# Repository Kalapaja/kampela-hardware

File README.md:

# Kampela

## Reasonably secure hardware signer for the [Polkadot](https://polkadot.network) ecosystem

### Hardware design schematics and supplementary files

##### Note on repo history

This repo has been extracted from https://github.com/Alzymologist/kampela in September 2023 as a part of the repo modularization effort.

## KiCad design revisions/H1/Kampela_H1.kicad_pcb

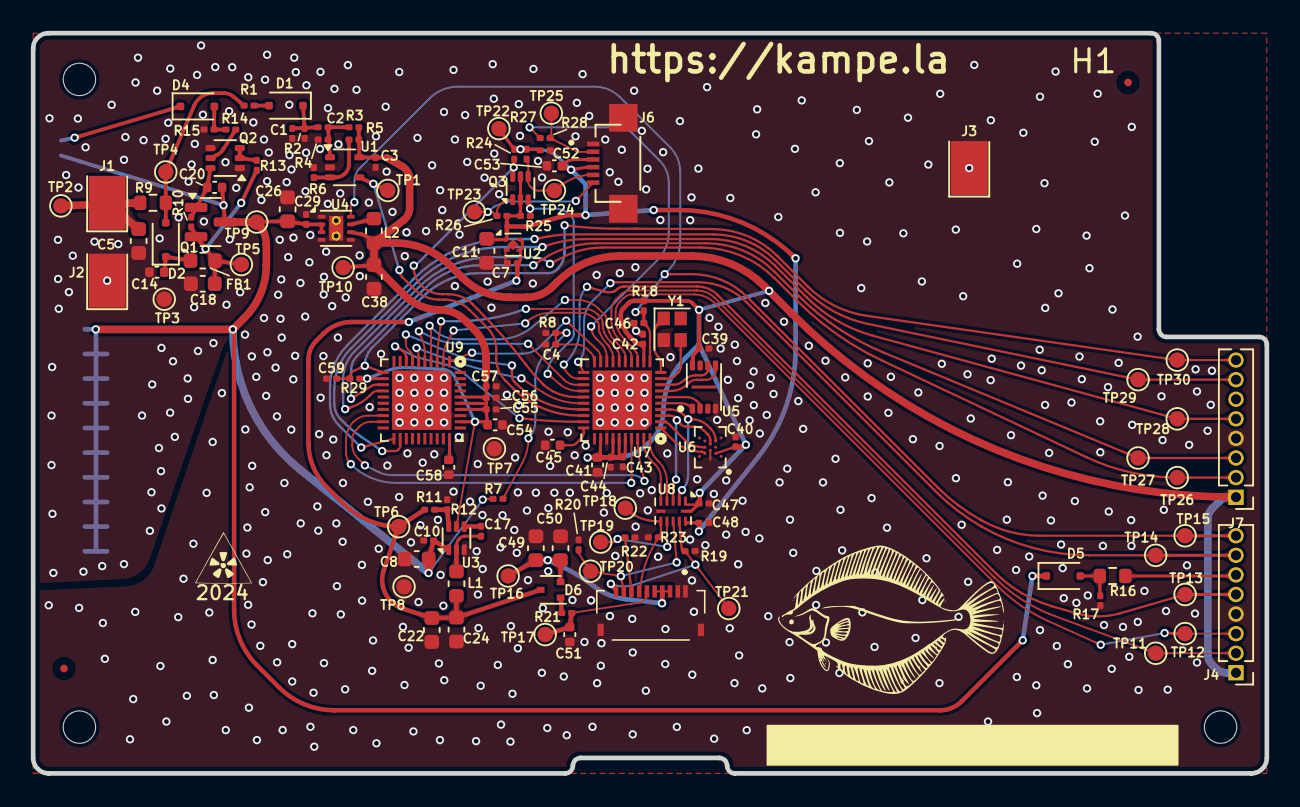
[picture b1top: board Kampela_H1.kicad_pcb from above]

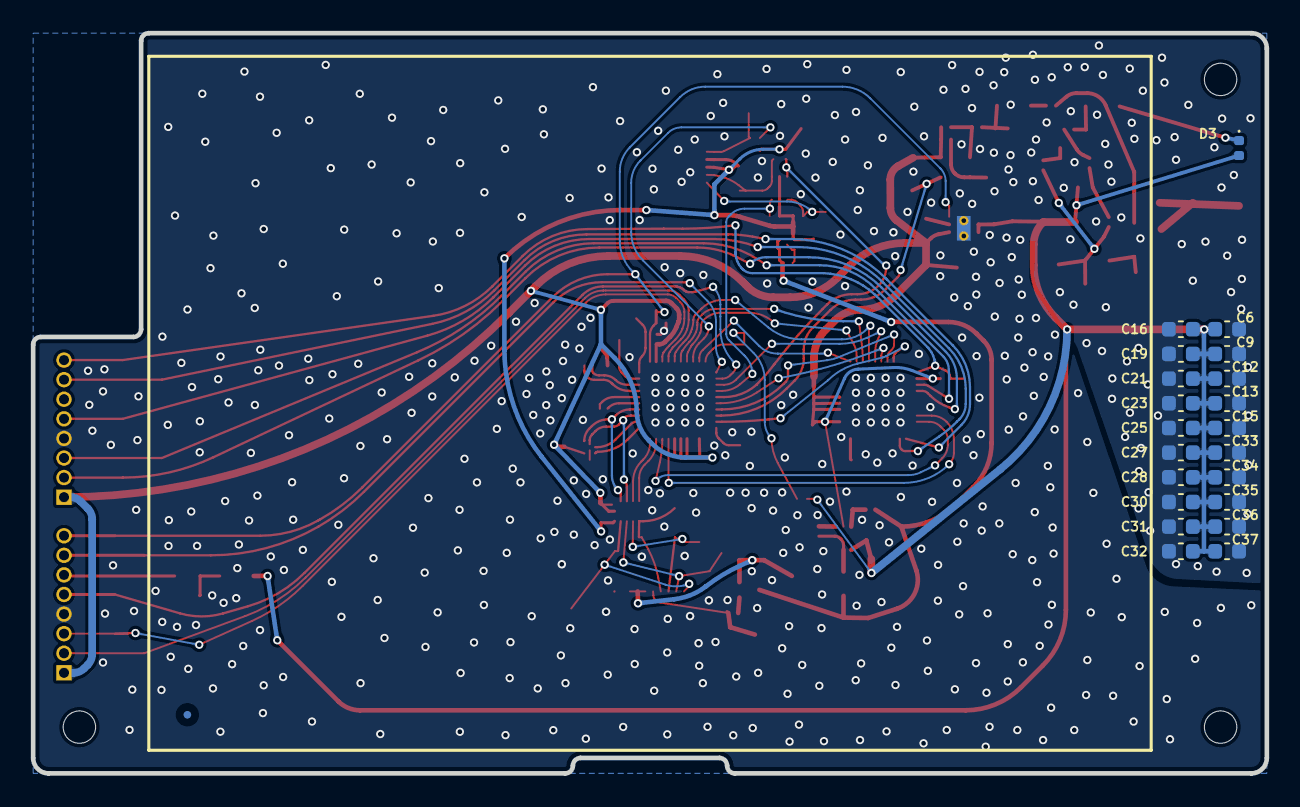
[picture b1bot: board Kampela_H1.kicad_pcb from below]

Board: 2 copper layers, 80.0 x 48.0 mm, 153 parts (22 on the bottom side), 73 nets.

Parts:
C1, C2: 100p; C_0201_0603Metric
C3, C4, C7, C10, C17, C29, C39, C40, C42, C43, C44, C46, C47, C48, C52, C55, C56, C57, C59: 0.1; C_0201_0603Metric
C5: 15p; C_0603_1608Metric
C6, C9, C12, C13, C15, C16, C19, C21, C23, C25, C27, C28, C30, C31, C32, C33, C34, C35, C36, C37: 22x16; C_0603_1608Metric
C8, C18, C26: 10x25; C_0603_1608Metric
C11, C22, C24, C38, C49, C50: 22x6.3; C_0603_1608Metric
C14, C20: 1x50; C_0402_1005Metric
C41, C45, C51, C53, C54, C58: 1x6.3; C_0402_1005Metric
D1, D5: BAT54WS; D_SOD-323F
D2: BAS70WS; D_SOD-323F
D3: RED; LED_0402_1005Metric
D4: D3Z13BF-7; D_SOD-323F
D6: BAT54AW; SOT-523
FB1: BLM18KG102SN1D; L_0603_1608Metric
FID1, FID2, FID4: Fiducial; Fiducial_0.5mm_Mask1.5mm
H1, H2, H3: MountingHole; MountingHole_2.1mm
J1, J2, J3: E_ANT; TestPoint_Pad_2.4x3.5mm
J4, J7: Conn_01x08; PinHeader_1x08_P1.27mm_Vertical
J5: FPC 10 TE1-2328702-0; TE_123287020
J6: TOUCH; HRS_FH34SRJ-6S-0.5SH(50)
L1, L2: 4.7uH; L_0603_1608Metric
Q1: NTR5105PT1G; SOT-23
Q2: BC846BS; SOT-363_SC-70-6
Q3: SSM6N35AFE; SOT-563
R1, R12, R15, R17, R18, R24, R25, R26, R27, R28, R29: 10K; R_0201_0603Metric
R2, R5, R11: 52.3K; R_0201_0603Metric
R3, R4, R10, R13, R19, R20, R22, R23: 100K; R_0201_0603Metric
R6, R14: 46.4K; R_0201_0603Metric
R7, R21: 1M; R_0201_0603Metric
R8: 150K; R_0201_0603Metric
R9, R16: 2.2; R_0603_1608Metric
TP1, TP2, TP3, TP4, TP5, TP6, TP7, TP8, TP9, TP10, TP11, TP12, TP13, TP14, TP15, TP16, TP17, TP18, TP19, TP20, TP21, TP22, TP23, TP24, TP25, TP26, TP27, TP28, TP29, TP30: TestPoint; TestPoint_Pad_D1.0mm
U1: LMV7271; SOT-353_SC-70-5
U2: NCP170AMX180TBG; OnSemi_XDFN4-1EP_1.0x1.0mm_EP0.52x0.52mm
U3: AP62250Z6; SOT-563
U4: TPS62171DSG; WSON-8-1EP_2x2mm_P0.5mm_EP0.9x1.6mm_ThermalVias
U5: APS6404L-SQN; SON-8-1EP_3x2mm_P0.5mm_EP1.4x1.6mm
U6: AT25XE321D-UUN-T; WLCSP 12-ball 3 x 2 x 3 Array
U7, U9: EFM32PG23B200F512IM40; QFN-40_EP_5x5_Pitch0.4mm
U8: TXU0104PW; Texas_R-PUQFN-N12
Y1: 39MHz; Crystal_SMD_2016-4Pin_2.0x1.6mm

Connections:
+1V8: C3.1, C38.1, C39.2, C40.2, C41.1, C42.2, C43.2, C44.2, C47.1, C54.1, C55.2, C56.2, C57.2, J4.1, J7.1, L2.2, R3.2, R5.2, R18.2, R29.2, TP10.1, U1.5 (V+), U3.5 (EN), U4.6 (VOS), U5.8 (VCC), U6.B2 (VCC), U7.12 (DVDD), U7.32 (VREGVDD), U7.34 (DVDD), U7.35 (AVDD), U7.36 (IOVDD), U8.1 (VCCA), U8.12 (OE), U9.12 (DVDD), U9.32 (VREGVDD), U9.34 (DVDD), U9.35 (AVDD), U9.36 (IOVDD)
+3V0: C11.2, C48.1, C52.2, C53.1, J6.3, J6.4, Q3.2 (G), Q3.5 (G), R24.2, R25.2, R26.2, R27.2, TP22.1, U2.1 (OUT), U8.11 (VCCB)
+5V: C7.2, C22.1, C24.2, D6.3, L1.2, R11.2, TP6.1, U2.3 (EN), U2.4 (IN)
/Display/CS: U7.40 (PD00), U8.4 (A3)
/Display/EXTIN: U7.39 (PD01), U8.5 (A4)
/Display/H_CS: J5.8, R22.2, TP19.1, U8.8 (B3)
/Display/H_EXTIN: J5.7, R23.2, TP18.1, U8.7 (B4)
/Display/H_SCK: J5.10, R19.2, TP21.1, U8.10 (B1)
/Display/H_SDI: J5.9, R20.2, TP20.1, U8.9 (B2)
/Display/INT: R28.1, U7.18 (PB01)
/Display/SCL: Q3.3 (D), R25.1, U7.24 (PA04)
/Display/SDA: Q3.6 (D), R24.1, U7.25 (PA05)
/Display/T_INT: J6.2, R28.2, TP25.1
/Display/T_SCL: J6.5, Q3.4 (S), R27.1, TP24.1
/Display/T_SDA: J6.6, Q3.1 (S), R26.1, TP23.1
/MCU SEC/ALEPH: U7.19 (PB00), U9.1 (PC00)
/MCU SEC/BET: U7.17 (PB02), U9.2 (PC01)
/MCU SEC/DALET: U7.15 (PB04), U9.4 (PC03)
/MCU SEC/DATA: TP1.1, U1.4, U7.28 (PA08)
/MCU SEC/E_MISO: U6.D4 (IO1/SO), U7.2 (PC01)
/MCU SEC/E_MOSI: U6.E3 (SI/IO0), U7.3 (PC02), U8.3 (A2)
/MCU SEC/E_SCK: U6.F2 (SCK), U7.4 (PC03), U8.2 (A1)
/MCU SEC/FLASH_CS: U6.B4 (~CS), U7.1 (PC00)
/MCU SEC/GIMEL: U7.16 (PB03), U9.3 (PC02)
/MCU SEC/HE: U7.23 (PA03), U9.5 (PC04)
/MCU SEC/HET: U7.29 (PA09), U9.8 (PC07)
/MCU SEC/P_GOOD: C46.2, J4.8, R18.1, TP15.1, U4.8 (PG), U7.11 (~RESET)
/MCU SEC/P_IN: J4.6, R16.1
/MCU SEC/RAM_CS: U5.1 (~CE), U7.5 (PC04)
/MCU SEC/RX: J4.2, TP11.1, U7.14 (PB05)
/MCU SEC/R_MISO: U5.2 (SO/SIO), U7.6 (PC05)
/MCU SEC/R_MOSI: U5.5 (SI/SIO), U7.7 (PC06)
/MCU SEC/R_SCK: U5.6 (SCLK), U7.8 (PC07)
/MCU SEC/SWDCK: J4.7, TP14.1, U7.21 (PA01)
/MCU SEC/SWDIO: J4.5, TP13.1, U7.22 (PA02)
/MCU SEC/TET: U7.38 (PD02), U9.19 (PB00)
/MCU SEC/TX: J4.3, TP12.1, U7.13 (PB06)
/MCU SEC/VAV: U7.26 (PA06), U9.6 (PC05)
/MCU SEC/V_CHK: C4.2, R7.1, R8.2, U7.20 (PA00)
/MCU SEC/YOD: U7.37 (PD03), U9.18 (PB01)
/MCU SEC/ZAYIN: U7.27 (PA07), U9.7 (PC06)
/MCU UI/P_GOOD: C59.2, J7.8, R29.1, TP30.1, U9.11 (~RESET)
/MCU UI/RX: J7.2, TP26.1, U9.14 (PB05)
/MCU UI/SWDCK: J7.7, TP29.1, U9.21 (PA01)
/MCU UI/SWDIO: J7.5, TP28.1, U9.22 (PA02)
/MCU UI/TX: J7.3, TP27.1, U9.13 (PB06)
/Power/OUT_DT: D2.2 (A), R1.1, R9.2, TP4.1
GND: C1.1, C3.2, C4.1, C5.2, C6.2, C7.1, C8.2, C9.2, C10.1, C11.1, C12.2, C13.2, C14.2, C15.2, C16.2, C18.2, C19.2, C21.2, C22.2, C23.2, C24.1, C25.2, C26.2, C27.2, C28.2, C29.1, C30.2, C31.2, C32.2, C33.2, C34.2, C35.2, C36.2, C37.2, C38.2, C39.1, C40.1, C41.2, C42.1, C43.1, C44.1, C45.2, C46.1, C47.2, C48.2, C49.1, C50.1, C51.2, C52.1, C53.2, C54.2, C55.1, C56.1, C57.1, C58.2, C59.1, J2.1, J3.1, J4.4, J5.1, J5.2, J5.MP1, J5.MP2, J6.1, J6.S2 (S), J7.4, Q2.1 (E1), Q2.4 (E2), R2.1, R4.1, R6.1, R8.1, R12.1, R15.1, R17.1, R19.1, R20.1, R22.1, R23.1, TP3.1, TP7.1, TP8.1, U1.2 (V-), U2.2 (GND), U2.5 (GND), U3.3 (GND), U4.1 (PGND), U4.4 (AGND), U4.5 (FB), U4.9 (PAD), U5.4 (VSS), U6.C3 (GND), U7.33 (VREGVSS), U7.41 (VSS), U8.6 (GND), U9.33 (VREGVSS), U9.41 (VSS), Y1.2
HV: C6.1, C8.1, C9.1, C10.2, C12.1, C13.1, C15.1, C16.1, C19.1, C20.2, C21.1, C23.1, C25.1, C26.1, C27.1, C28.1, C29.2, C30.1, C31.1, C32.1, C33.1, C34.1, C35.1, C36.1, C37.1, D3.2 (A), D5.1 (K), Q1.3 (D), R7.2, TP9.1, U3.1 (VIN), U4.2 (VIN), U4.3 (EN)
unnamed: C49.2, C50.2, D6.2, J5.3, J5.4, J5.5, TP16.1
unnamed: C51.1, J5.6, R21.1, TP17.1
unnamed: D1.2 (A), R1.2
unnamed: C1.2, C2.2, D1.1 (K), R2.2
unnamed: C14.1, D2.1 (K), FB1.2
unnamed: D3.1 (K), D4.1 (K)
unnamed: D4.2 (A), R14.1, R15.2
unnamed: D5.2 (A), R16.2, R17.2
unnamed: D6.1, R21.2
unnamed: C5.1, J1.1, R9.1, TP2.1
unnamed: C20.1, Q1.1 (G), Q2.6 (C1), R10.2
unnamed: C18.1, FB1.1, Q1.2 (S), R10.1, R13.2, TP5.1
unnamed: Q2.2 (B1), Q2.3 (C2), R13.1
unnamed: Q2.5 (B2), R14.2
unnamed: C2.1, R3.1, R4.2, U1.1 (+)
unnamed: R5.1, R6.2, U1.3 (-)
unnamed: C17.1, U3.4 (BST)
unnamed: R11.1, R12.2, U3.6 (FB)
unnamed: C17.2, L1.1, U3.2 (SW)
unnamed: L2.1, U4.7 (SW)
unnamed: C45.1, U7.30 (CAP)
unnamed: U7.9 (HFXTAL_I), Y1.3
unnamed: U7.10 (HFXTAL_O), Y1.1
unnamed: C58.1, U9.30 (CAP)

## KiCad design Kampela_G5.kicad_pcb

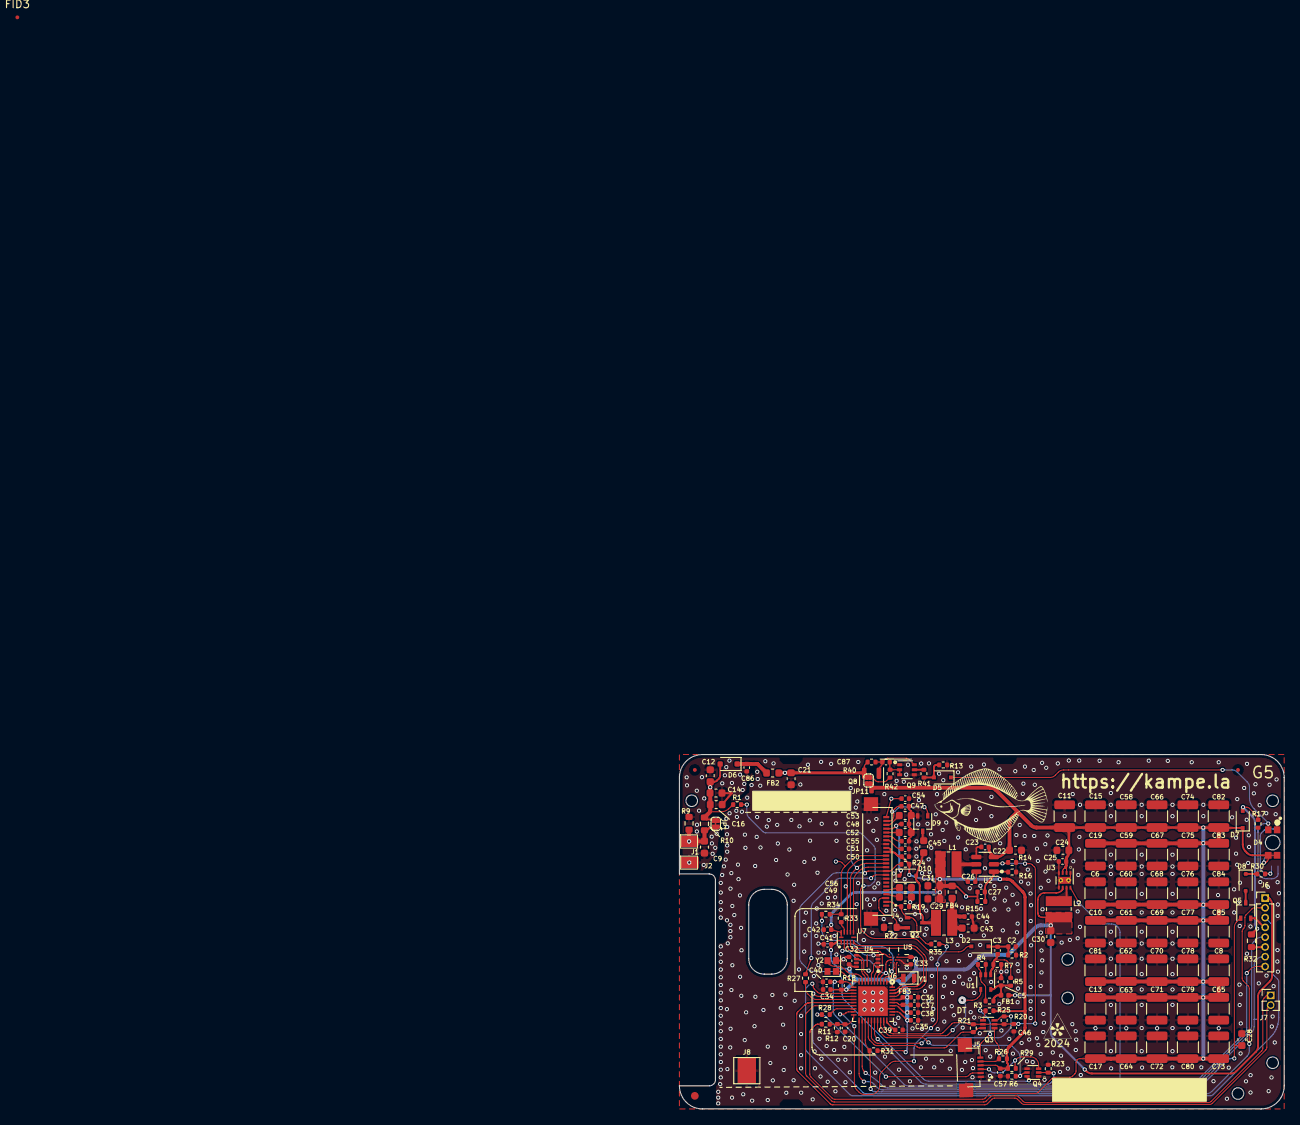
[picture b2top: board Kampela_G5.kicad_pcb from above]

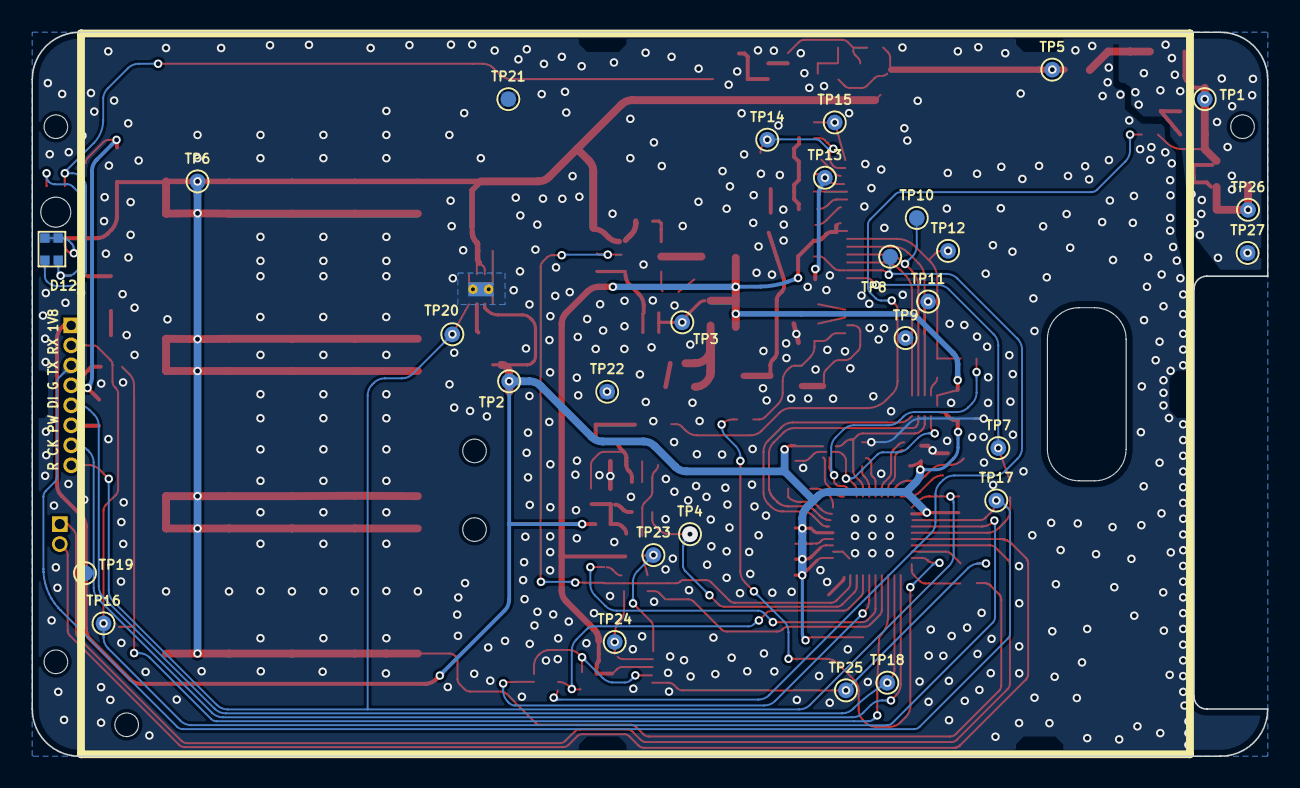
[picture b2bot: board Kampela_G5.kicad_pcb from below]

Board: 2 copper layers, 78.5 x 46.0 mm, 194 parts (28 on the bottom side), 86 nets.

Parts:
C2, C3, C27: 100p; C_0402_1005Metric
C5, C20, C23, C25, C26, C32, C33, C35, C36, C37, C38, C40, C41, C42, C46: 0.1u; C_0402_1005Metric
C6, C8, C10, C11, C13, C15, C17, C19, C58, C59, C60, C61, C62, C63, C64, C65, C66, C67, C68, C69, C70, C71, C72, C73, C74, C75, C76, C77, C78, C79, C80, C81, C82, C83, C84, C85: 47x16; C_1210_3225Metric
C9: 15p; C_0603_1608Metric
C12, C14: 47; C_0603_1608Metric
C16: 100; C_0603_1608Metric
C21: 10x25; C_0603_1608Metric
C22, C24: 10x16; C_0603_1608Metric
C28, C43, C45, C49, C52, C53, C56: 4.7x25; C_0603_1608Metric
C29, C30, C31: 22x6.3; C_0603_1608Metric
C34, C39, C50, C51, C55, C57: 1x6.3; C_0402_1005Metric
C44: 0.1; C_0402_1005Metric
C47, C48, C54, C86, C87: 1x50; C_0402_1005Metric
D2, D7, D10: BAT54WS; D_SOD-323F
D4: 156125RG73000; SMD4_WL-SBRW-1205_REV-MOUNT_WRE
D5: D3Z13BF-7; D_SOD-323F
D6: BAS70WS; D_SOD-323F
D8: D3Z5V1BF-7; D_SOD-323F
D9: BAS70-04W; SOT-323_SC-70
D12: SB0603WC01-RG; LED_DUAL_0603
FB1, FB3: BLM15AG102SZ1D; L_0402_1005Metric
FB2, FB4: BLM18KG102SN1D; L_0603_1608Metric
FID1, FID2, FID3, FID4: Fiducial; Fiducial_0.5mm_Mask1.5mm
H1, H2, H3: MountingHole; MountingHole_2.1mm
J1, J2, J8: E_ANT; TestPoint_Pad_2.4x3.5mm
J4: E2154CS0C1; GDEY027T91-T01_bended
J5: TOUCH; HRS_FH34SRJ-6S-0.5SH(50)
J6: Conn_01x08; PinHeader_1x08_P1.27mm_Vertical
J7: Conn_01x02; PinHeader_1x02_P1.27mm_Vertical
JP1, JP11: SolderJumper_2_Open; SolderJumper_0.8.x1mm
L1: 3.3uH; L_Wuerth_MAPI-3015
L2: 2.2uH; L_Wuerth_MAPI-3015
L3: NR3015T100M; L_Wuerth_MAPI-3015
Q2: PMF250XNEX; SOT-323_SC-70
Q3, Q4: SSM6N35AFE; SOT-563
Q5: NX138BKWX; SOT-323_SC-70
Q8: NTR5105PT1G; SOT-23
Q9: BC846BS; SOT-363_SC-70-6
R1, R6, R17, R18, R23, R24, R25, R26, R27, R28, R29: 10K; R_0402_1005Metric
R2, R3, R16: 52.3K; R_0402_1005Metric
R4, R41: 47K; R_0402_1005Metric
R5, R7, R40, R42: 100K; R_0402_1005Metric
R9: 1K; R_0603_1608Metric
R10, R32: 2.2; R_0603_1608Metric
R11: 976K; R_0402_1005Metric
R12, R14: 150K; R_0402_1005Metric
R13, R20, R21, R34, R35: 1K; R_0402_1005Metric
R15: 130K; R_0402_1005Metric
R19, R31: 470K; R_0402_1005Metric
R22: 0.47R; R_0603_1608Metric
R30, R33: 100; R_0402_1005Metric
TP1, TP2, TP3, TP4, TP5, TP6, TP7, TP8, TP9, TP10, TP11, TP12, TP13, TP14, TP15, TP16, TP17, TP18, TP19, TP20, TP21, TP22, TP23, TP24, TP25, TP26, TP27: TestPoint; TestPoint_Pad_D1.0mm
U1: LMV7271; SOT-353_SC-70-5
U2: AP63200WU; TSOT-23-6
U3: TPS62171DSG; WSON-8-1EP_2x2mm_P0.5mm_EP0.9x1.6mm_ThermalVias
U4: APS6404L-SQN; SON-8-1EP_3x2mm_P0.5mm_EP1.4x1.6mm
U5: AT25XE321D-UUN-T; WLCSP 12-ball 3 x 2 x 3 Array
U6: EFM32PG23B200F512IM40; QFN-40_EP_5x5_Pitch0.4mm
U7: TXU0104PW; Texas_R-PUQFN-N12
Y1: FC2012AN; Crystal_SMD_2012-2Pin_2.0x1.2mm
Y2: 39MHz; Crystal_SMD_2016-4Pin_2.0x1.6mm

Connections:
+1V8: C30.2, C32.1, C33.1, C34.2, C35.1, C36.1, C38.1, C41.2, FB1.1, FB3.2, J6.1, L2.2, R18.2, R31.1, TP2.1, U3.6 (VOS), U4.8 (VCC), U5.B2 (VCC), U6.12 (DVDD), U6.32 (VREGVDD), U6.34 (DVDD), U6.36 (IOVDD), U7.1 (VCCA)
+2V8: C27.1, C29.2, C31.2, C42.1, C50.2, C57.1, FB4.2, J4.15, J4.16, J5.4, L1.2, R15.1, R24.2, R25.1, R26.1, R29.2, TP3.1, U7.11 (VCCB), U7.12 (OE)
/Cap Block/HV: C6.2, C8.2, C10.2, C11.2, C13.2, C15.2, C17.2, C19.2, C22.2, C23.1, C24.2, C25.1, C58.2, C59.2, C60.2, C61.2, C62.2, C63.2, C64.2, C65.2, C66.2, C67.2, C68.2, C69.2, C70.2, C71.2, C72.2, C73.2, C74.2, C75.2, C76.2, C77.2, C78.2, C79.2, C80.2, C81.2, C82.2, C83.2, C84.2, C85.2, D4.3 (A2), D4.4 (A1), D7.1 (K), D12.2 (K1), D12.4 (K2), JP11.1 (A), Q8.3 (D), R11.1, TP6.1, U2.3 (IN), U3.2 (VIN), U3.3 (EN)
/Display/2V8_EN: C46.1, Q3.2 (G), Q3.5 (G), R14.2, R20.2, R21.2, U2.2 (EN), U6.29 (PA09)
/Display/BUSY: R27.2, U6.15 (PB04)
/Display/E_BUSY: J4.9, R27.1, TP7.1
/Display/E_CS: U6.38 (PD02), U7.4 (A3)
/Display/E_D/C: U6.37 (PD03), U7.5 (A4)
/Display/E_MISO: R34.1, U5.D4 (IO1/SO), U6.2 (PC01)
/Display/E_RES: J4.10, Q4.6 (D), R24.1, TP8.1
/Display/E_SCK: U5.F2 (SCK), U6.4 (PC03), U7.3 (A2)
/Display/E_SDI: U5.E3 (SI/IO0), U6.3 (PC02), U7.2 (A1)
/Display/GDR: J4.2, Q2.1 (G), R19.1, R35.1
/Display/H_CS: J4.12, TP10.1, U7.8 (B3)
/Display/H_D/C: J4.11, TP9.1, U7.7 (B4)
/Display/H_SCK: J4.13, TP11.1, U7.9 (B2)
/Display/H_SDI: J4.14, R33.1, R34.2, TP12.1
/Display/INT: R28.2, U6.18 (PB01)
/Display/POW: C43.2, C44.1, FB4.1, L3.1
/Display/PREVGH: C48.1, D10.1 (K), J4.21, TP13.1
/Display/PREVGL: C47.1, D9.1, J4.23, TP14.1
/Display/RES: Q4.2 (G), R23.2, U6.26 (PA06)
/Display/RESE: J4.3, Q2.2 (S), R22.1
/Display/RES_TC: Q4.5 (G), R6.2, U6.27 (PA07)
/Display/SCL: Q3.3 (D), R21.1, U6.24 (PA04)
/Display/SDA: Q3.6 (D), R20.1, U6.25 (PA05)
/Display/T_INT: J5.2, R28.1, TP25.1
/Display/T_RES: J5.3, Q4.3 (D), R29.1
/Display/T_SCL: J5.5, Q3.4 (S), R26.2, TP24.1
/Display/T_SDA: J5.6, Q3.1 (S), R25.2, TP23.1
/Display/VCOM: C54.2, J4.24, TP15.1
/MCU/DATA: TP4.1, U1.4, U6.28 (PA08)
/MCU/FLASH_CS: U5.B4 (~CS), U6.1 (PC00)
/MCU/P_GOOD: C40.1, J6.8, R18.1, TP20.1, U3.8 (PG), U6.11 (~RESET)
/MCU/P_IN: J6.6, R32.1
/MCU/RAM_CS: U4.1 (~CE), U6.5 (PC04)
/MCU/RX: J6.2, TP16.1, U6.14 (PB05)
/MCU/R_MISO: U4.2 (SO/SIO), U6.6 (PC05)
/MCU/R_MOSI: U4.5 (SI/SIO), U6.7 (PC06)
/MCU/R_SCK: U4.6 (SCLK), U6.8 (PC07)
/MCU/SWDCK: J6.7, TP19.1, U6.21 (PA01)
/MCU/SWDIO: J6.5, TP18.1, U6.22 (PA02)
/MCU/TX: J6.3, TP17.1, U6.13 (PB06)
/MCU/V_CHK: C20.1, R11.2, R12.1, U6.20 (PA00)
/MCU/~MCU_OK: C28.2, Q5.1 (G), R31.2, U6.23 (PA03)
/Power/IN_DT: C12.1, C14.1, C16.1, D6.2 (A), JP1.1 (A), R1.1, R10.2, TP1.1
GND: C2.2, C5.1, C6.1, C8.1, C9.2, C10.1, C11.1, C12.2, C13.1, C14.2, C15.1, C16.2, C17.1, C19.1, C20.2, C21.1, C22.1, C23.2, C24.1, C25.2, C28.1, C29.1, C30.1, C31.1, C32.2, C33.2, C34.1, C35.2, C36.2, C37.2, C38.2, C39.1, C40.2, C41.1, C42.2, C43.1, C44.2, C46.2, C47.2, C48.2, C49.1, C50.1, C51.1, C52.1, C53.1, C54.1, C55.1, C56.1, C57.2, C58.1, C59.1, C60.1, C61.1, C62.1, C63.1, C64.1, C65.1, C66.1, C67.1, C68.1, C69.1, C70.1, C71.1, C72.1, C73.1, C74.1, C75.1, C76.1, C77.1, C78.1, C79.1, C80.1, C81.1, C82.1, C83.1, C84.1, C85.1, C86.2, D9.2, J2.1, J4.8, J4.17, J4.S2 (S), J5.1, J5.S2 (S), J6.4, J8.1, Q4.1 (S), Q4.4 (S), Q5.2 (S), Q9.1 (E1), Q9.4 (E2), R2.2, R4.2, R6.1, R7.2, R9.1, R12.2, R13.2, R14.1, R16.2, R17.2, R19.2, R22.2, R23.1, TP21.1, TP22.1, TP27.1, U1.2 (V-), U2.4 (GND), U3.1 (PGND), U3.4 (AGND), U3.5 (FB), U3.9 (PAD), U4.4 (VSS), U5.C3 (GND), U6.33 (VREGVSS), U6.41 (VSS), U7.6 (GND), Y2.2
unnamed: C45.1, D9.3
unnamed: D2.2 (A), R1.2
unnamed: C2.1, C3.2, D2.1 (K), R2.1
unnamed: D5.2 (A), R13.1, R41.2
unnamed: C86.1, D6.1 (K), FB2.2
unnamed: D7.2 (A), R17.1, R32.2
unnamed: D8.2 (A), Q5.3 (D)
unnamed: D8.1 (K), R30.2
unnamed: C45.2, D10.2 (A), L3.2, Q2.3 (D)
unnamed: D4.2 (K2), D5.1 (K), D12.1 (A1)
unnamed: D4.1 (K1), D12.3 (A2), R30.1
unnamed: C9.1, J1.1, JP1.2 (B), R9.2, R10.1, TP26.1
unnamed: C49.2, J4.4
unnamed: C56.2, J4.5
unnamed: C51.2, J4.18
unnamed: C55.2, J4.19
unnamed: C52.2, J4.20
unnamed: C53.2, J4.22
unnamed: J7.1, U6.17 (PB02)
unnamed: J7.2, U6.16 (PB03)
unnamed: C21.2, FB2.1, JP11.2 (B), Q8.2 (S), R40.1, R42.1, TP5.1
unnamed: C87.1, Q8.1 (G), Q9.6 (C1), R40.2
unnamed: C87.2, Q9.2 (B1), Q9.3 (C2), R42.2
unnamed: Q9.5 (B2), R41.1
unnamed: C3.1, R5.2, R7.1, U1.1 (+)
unnamed: R3.2, R4.1, U1.3 (-)
unnamed: C5.2, FB1.2, R3.1, R5.1, U1.5 (V+)
unnamed: C26.2, U2.6 (BST)
unnamed: C27.2, R15.2, R16.1, U2.1 (FB)
unnamed: C26.1, L1.1, U2.5 (SW)
unnamed: L2.1, U3.7 (SW)
unnamed: C37.1, FB3.1, U6.35 (AVDD)
unnamed: C39.2, U6.30 (CAP)
unnamed: U6.9 (HFXTAL_I), Y2.3
unnamed: U6.10 (HFXTAL_O), Y2.1
unnamed: R35.2, U6.19 (PB00)
unnamed: U6.40 (PD00), Y1.2
unnamed: U6.39 (PD01), Y1.1
unnamed: R33.2, U7.10 (B1)

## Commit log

2023-01-23 feat: initial hardware development (#22)
    * chore: update gitignote
    * feat: coil and screen prototype pcb
    * docs: readme
    * docs: document schematics
    * feat: add mock case models
    * feat: casing design solution
2023-03-26 feat: D1 mechanical design (#39)
    * D1 iteration enclosure design proccess
    * D1 iteration hardware process
    * D1 iteration hardware process
    * Update README.md
    * Update README.md
    * D1 small fixes
2023-06-19 major: port system crate to E hardware edition (#53)
    * feat: E1 schematics
    * chore: backup C1 kampela-system version
    * feat: change pin locations
    * feat: UI works on E
2023-09-14 Restored GPLv3 license from the original repo
2023-09-14 Restored .gitignore from the original repo
2023-09-14 Added README.md
2023-09-14 G2 revision
    G2 revision = Kampela development kit
    Features:
    - electronics is more stable and reliable
    - better power harvesting efficiency
    - fixed a touchscreen instability with powerful NFC transmitters
    - mechanical layout improved for low-volume productions for a devkit batch
2023-09-14 previews added
2023-09-14 README fixed
2024-11-01 G5 revision
2024-11-01 Next revision
2024-11-26 Add G5 revision enclosure
2024-11-26 fix: restore kampela enclosure
2024-11-28 Add files via upload
    fix: restore the kampela enclosure file
2025-05-06 Create readme.md and new layout folder
2025-05-06 Create readme.md and mass production folder
2025-05-06 Adding enclosure manufacturing form files.
2025-05-06 Add "New Layout" enclosure files
2025-05-29 Add H1 revision (dual head)
